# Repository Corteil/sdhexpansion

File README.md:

# SD Hexpansion

A Hexpansion for the [EMFCamp Tildagon badge](https://tildagon.badge.emfcamp.org/) which adds a MicroSD card socket in SPI mode.  The Hexpansion has an 8kB EEPROM and has a load switch for the SD card (there are a bunch of reasons SD cards can get "stuck" and are only recoverable by power cycling).  Details of the hardware design can be found in [the hardware docs](HARDWARE.md).

## Using your SD Hexpansion

To make use of the hexpansion right away without writing any of your own code, get an micro SD card
and plug it into a computer.  The card needs to be formatted as a FAT filesystem, that's what most
cards will be.

1. Make a folder on the SD card called `sdcard_apps`
2. Inside this folder you can place standard [Tildagon apps](https://tildagon.badge.emfcamp.org/tildagon-apps/)
3. Safely remove the SD card from your computer
4. Plug it into your hexpansion
5. Power up the badge
6. The hexpansion app for your SD card reader should pop up with three menu items "Mount", "Remove" and "Format".  Select the "Mount" option then exit the app (button F on the badge front-panel).
7. Now look at the bottom of the list of apps on the launcher, the apps on your SD card should be there and ready to go!

### Why "sdcard_apps"?
There's a [bug in micropython](https://github.com/emfcamp/badge-2024-software/issues/334) which means that `import` doesn't work properly if it includes the mount point of a FAT filesystem.  To work around this the driver EEPROM adds the mount-point (`sdcard` which is the name of the folder on the badge where all the files on your card will appear) to the system path.  That means that when `import` is run it searches in the SD card for micropython code.  If the folder where all the apps were installed on the SD card was just called `apps` it would have the same name as the default location on the badge itself and the software wouldn't know which of the two `apps` folders to look in.  The paths discussed here aren't magic, they are all defined in the EEPROM app which is run when the hexpansion is plugged in.

## Driver EEPROM

### Driver Hacking

If you want to modify the code that is in the driver app, you will need to follow the steps
here to get the modified code onto the hexpansion.

To squeeze the most out of the 8kB EEPROM on the hexpansion I've been compiling to
a `*.mpy` file, I've done this already but if you want to modify it you'll need to
do this step.  You need the [mpy-cross](https://pypi.org/project/mpy-cross/) tool
then you can simply run

    mpy-cross app.py

To setup a blank SD Hexpansion you need to plug it in to your badge and connect to the badge using [mpremote](https://docs.micropython.org/en/latest/reference/mpremote.html).

On the host change into the `app` directory of a checkout of this repository and run:

    mpremote mount .

This will connect to the running micropython system on your badge, hit `Ctrl-C` to
interrupt the normal OS and get a Python prompt.  Make sure the SDHexpansion is in port 2 (the right hand side) and short out the write-protect pins to allow the EEPROM to be overwritten (I normally use a pair of tweezers, but a jumper wire or even a bent paperclip will probably do).  Then on the mpremote terminal type:

    import prepare_eeprom

And that's it, the code runs on import and should have set up the EEPROM and copied the app.  Reboop the badge and you should get a new app offering to let you "Mount", "Remove" or "Format" the SD card.

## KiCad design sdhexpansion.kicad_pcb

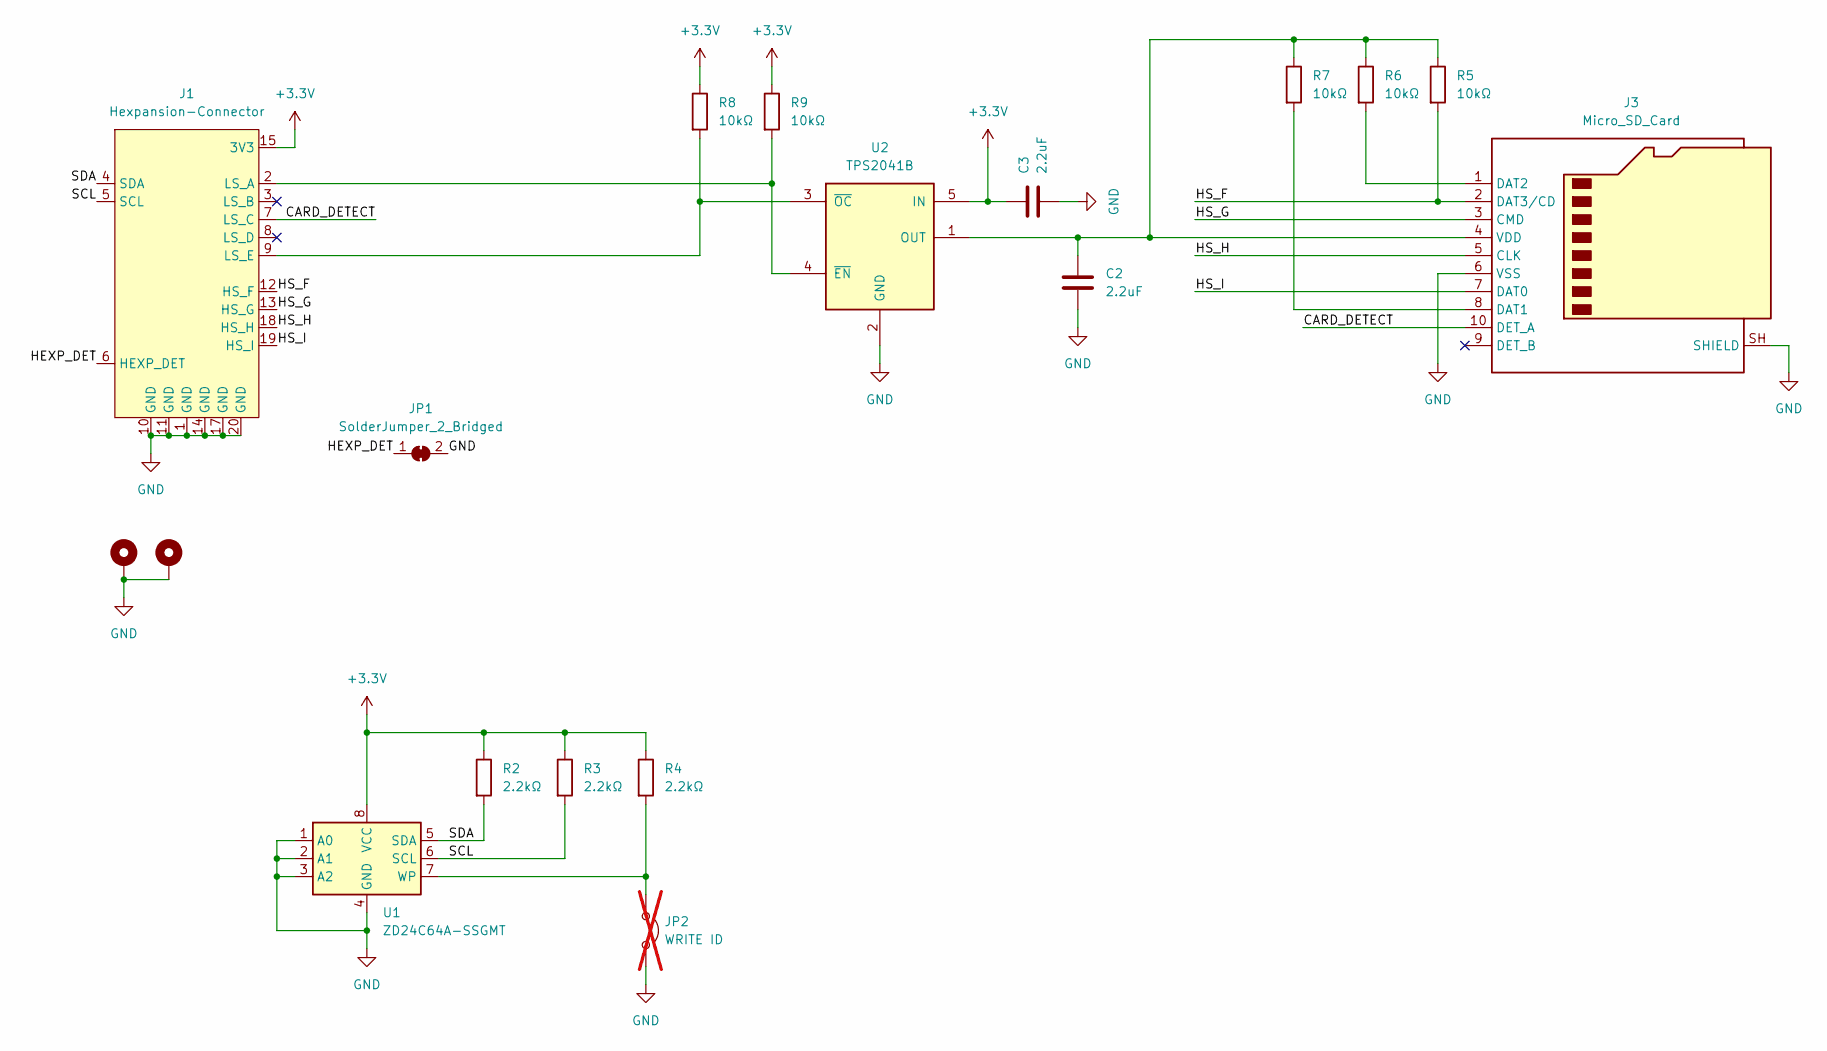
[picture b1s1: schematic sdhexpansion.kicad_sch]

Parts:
C2, C3: 2.2uF; C_0603_1608Metric; LCSC C23630
H1, H2: MountingHole_Pad; MountingHole_2.2mm_M2_Pad_Via
J1: Hexpansion-Connector; hexpansion-edge-connector
J3: Micro_SD_Card; MICRO-SD_XKTF-001C; LCSC C1121870
JP1: SolderJumper_2_Bridged; SolderJumper-2_P1.3mm_Bridged_RoundedPad1.0x1.5mm
JP2: WRITE ID; PinHeader_1x02_P2.54mm_Vertical; not fitted
R2, R3, R4: 2.2kΩ; R_0603_1608Metric; LCSC C4190
R5, R6, R7, R8, R9: 10kΩ; R_0603_1608Metric; LCSC C25804
U1: ZD24C64A-SSGMT; SOIC-8_3.9x4.9mm_P1.27mm; LCSC C2896793
U2: TPS2041B; SOT-23-5; LCSC C24593

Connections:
+3.3V: C3.2, J1.15 (3V3), J1.16 (3V3), R2.1, R3.1, R4.1, R8.1, R9.1, U1.8 (VCC), U2.5 (IN)
/CARD_DETECT: J1.7 (LS_C), J3.10 (DET_A)
/HEXP_DET: J1.6 (HEXP_DET), JP1.1 (A)
/HS_F: J1.12 (HS_F), J3.2 (DAT3/CD), R5.2
/HS_G: J1.13 (HS_G), J3.3 (CMD)
/HS_H: J1.18 (HS_H), J3.5 (CLK)
/HS_I: J1.19 (HS_I), J3.7 (DAT0)
/SCL: J1.5 (SCL), R3.2, U1.6 (SCL)
/SDA: J1.4 (SDA), R2.2, U1.5 (SDA)
GND: C2.1, C3.1, H1.1 (1_1), H2.1 (1_1), J1.1 (GND), J1.10 (GND), J1.11 (GND), J1.14 (GND), J1.17 (GND), J1.20 (GND), J3.6 (VSS), J3.SH (SHIELD), JP1.2 (B), JP2.2 (B), U1.1 (A0), U1.2 (A1), U1.3 (A2), U1.4 (GND), U2.2 (GND)
unnamed: J1.2 (LS_A), R9.2, U2.4 (~EN)
unnamed: J1.9 (LS_E), R8.2, U2.3 (~OC)
unnamed: J3.8 (DAT1), R7.2
unnamed: J3.1 (DAT2), R6.2
unnamed: C2.2, J3.4 (VDD), R5.1, R6.1, R7.1, U2.1 (OUT)
unnamed: JP2.1 (A), R4.2, U1.7 (WP)

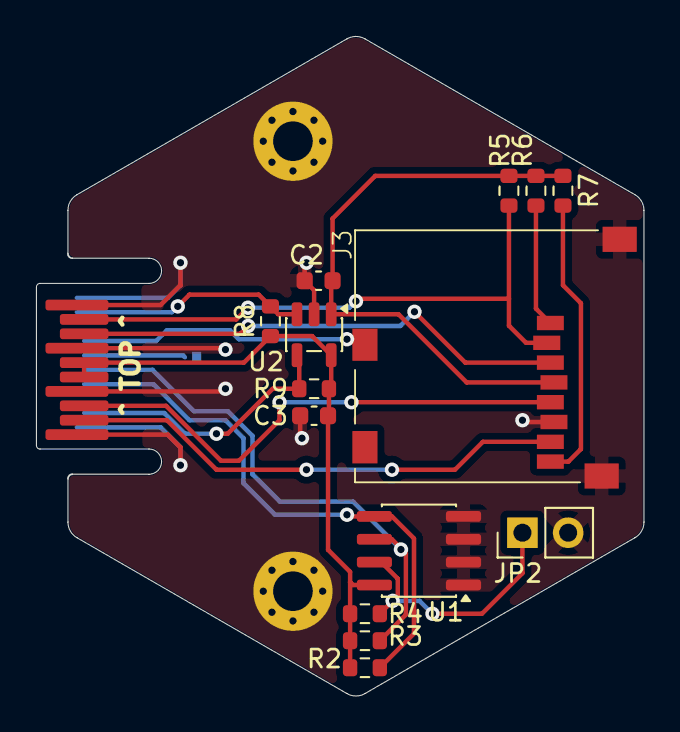
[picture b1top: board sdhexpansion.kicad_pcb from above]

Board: 2 copper layers, 33.7 x 36.6 mm, 18 parts (1 on the bottom side), 16 nets.

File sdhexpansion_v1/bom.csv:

Comment,Designator,Footprint,LCSC
2.2uF,"C2,C3",Capacitor_SMD:C_0603_1608Metric,C23630
2.2kΩ,"R2,R3,R4",Resistor_SMD:R_0603_1608Metric,C4190
Micro_SD_Card,J3,extras:MICRO-SD_XKTF-001C,C1121870
10kΩ,"R5,R6,R7,R8,R9",Resistor_SMD:R_0603_1608Metric,C25804
ZD24C64A-SSGMT,U1,Package_SO:SOIC-8_3.9x4.9mm_P1.27mm,C2896793
TPS2041B,U2,Package_TO_SOT_SMD:SOT-23-5,C24593

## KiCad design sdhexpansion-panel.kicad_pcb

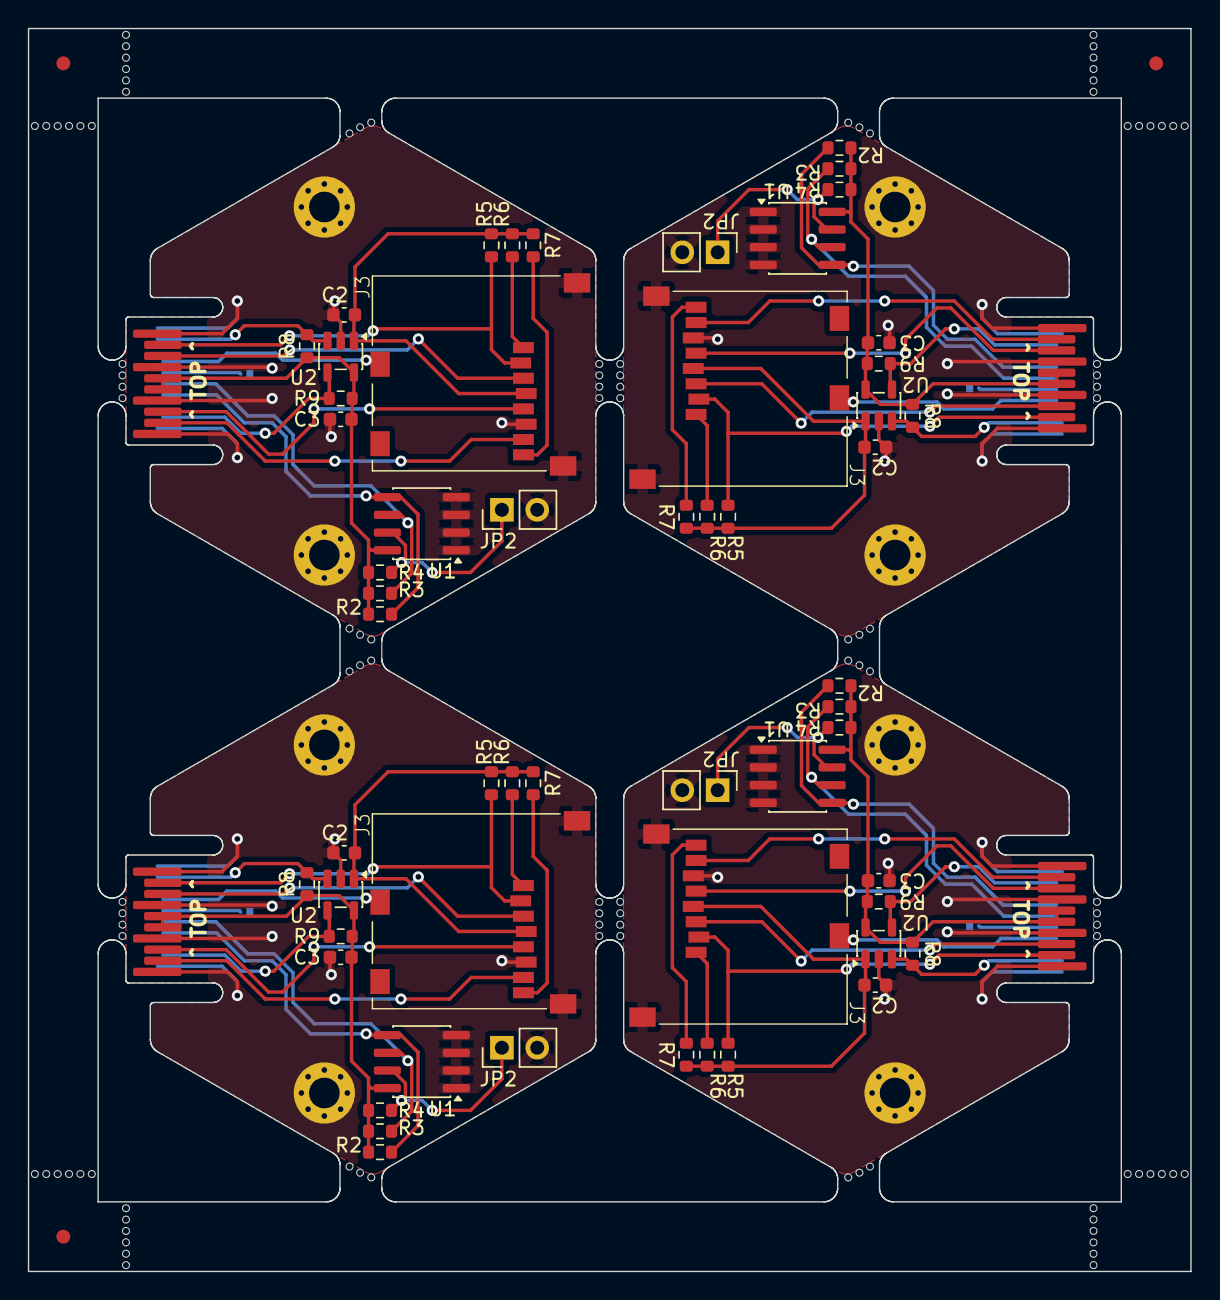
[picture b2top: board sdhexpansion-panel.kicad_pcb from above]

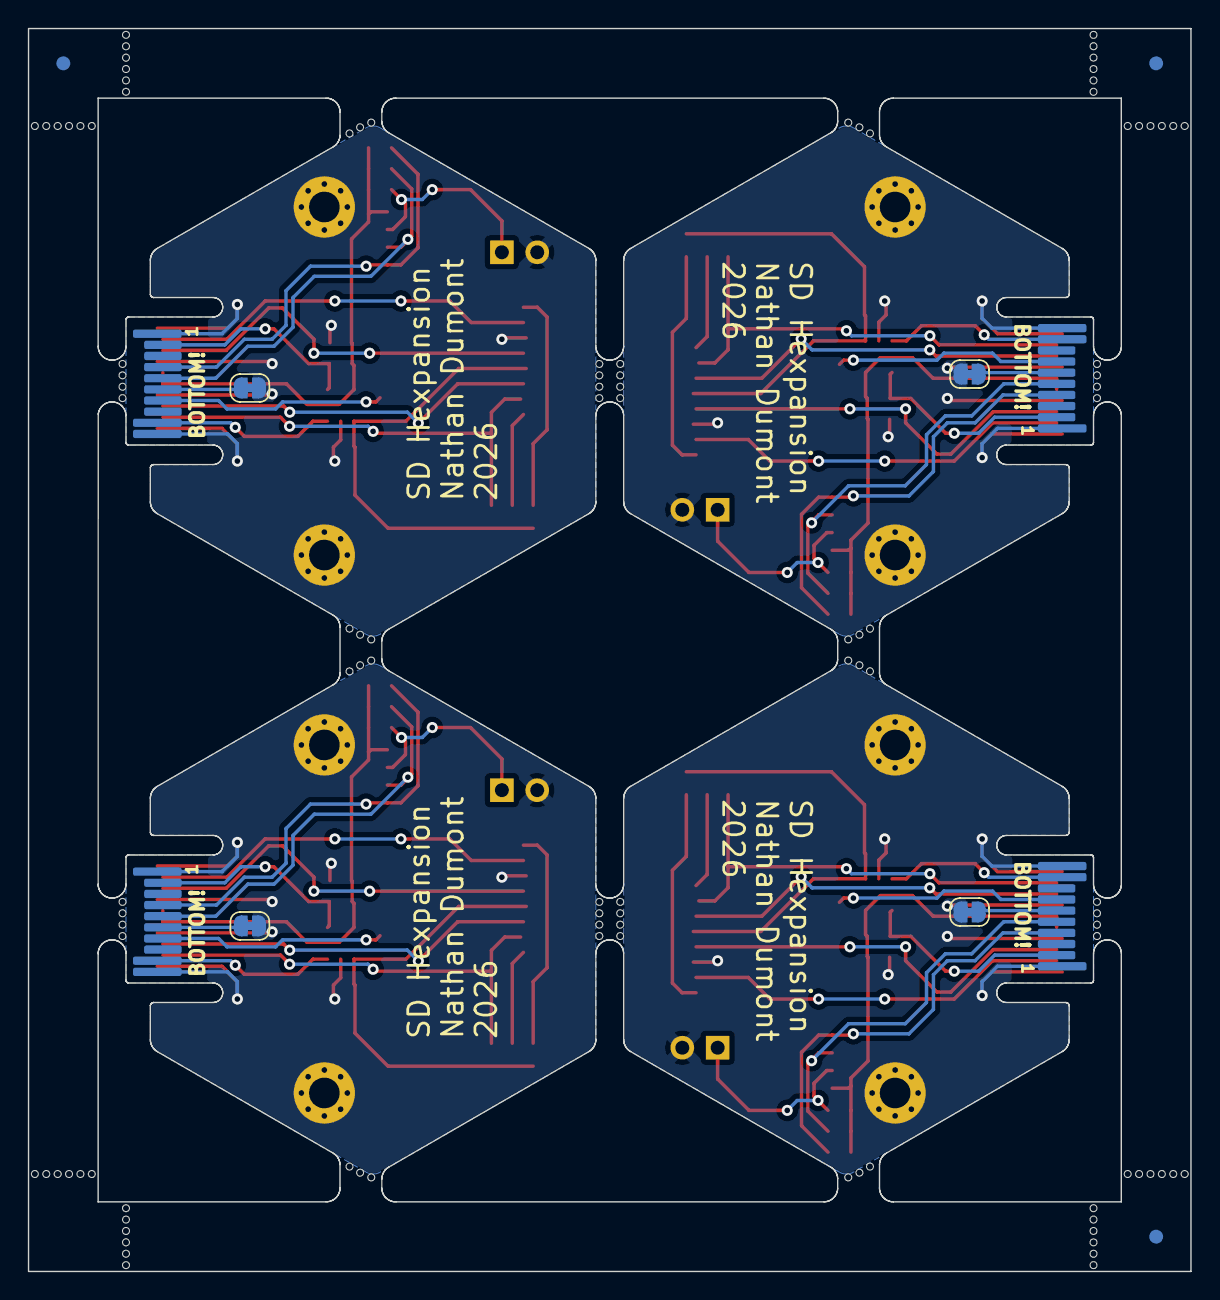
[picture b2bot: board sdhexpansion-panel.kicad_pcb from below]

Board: 2 copper layers, 83.5 x 89.3 mm, 182 parts (7 on the bottom side), 64 nets.

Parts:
C2, C2#2, C2#3, C2#4, C3, C3#2, C3#3, C3#4: 2.2uF; C_0603_1608Metric
H1, H1#2, H1#3, H1#4, H2, H2#2, H2#3, H2#4: MountingHole_Pad; MountingHole_2.2mm_M2_Pad_Via
J1, J1#2, J1#3, J1#4: Hexpansion-Connector; hexpansion-edge-connector
J3, J3#2, J3#3, J3#4: Micro_SD_Card; MICRO-SD_XKTF-001C
JP1, JP1#2, JP1#3, JP1#4: SolderJumper_2_Bridged; SolderJumper-2_P1.3mm_Bridged_RoundedPad1.0x1.5mm
JP2, JP2#2, JP2#3, JP2#4: WRITE ID; PinHeader_1x02_P2.54mm_Vertical
KiKit_FID_B_1, KiKit_FID_B_2, KiKit_FID_B_3: Fiducial
KiKit_FID_T_1, KiKit_FID_T_2, KiKit_FID_T_3: Fiducial
KiKit_MB_1_5, KiKit_MB_1_6, KiKit_MB_1_7, KiKit_MB_1_8, KiKit_MB_2_5, KiKit_MB_2_6, KiKit_MB_2_7, KiKit_MB_2_8, KiKit_MB_3_5, KiKit_MB_3_6, KiKit_MB_3_7, KiKit_MB_4_5, KiKit_MB_4_6, KiKit_MB_4_7, KiKit_MB_5_5, KiKit_MB_5_6, KiKit_MB_5_7, KiKit_MB_5_8, KiKit_MB_6_5, KiKit_MB_6_6, KiKit_MB_6_7, KiKit_MB_6_8, KiKit_MB_7_5, KiKit_MB_7_6, KiKit_MB_7_7, KiKit_MB_8_5, KiKit_MB_8_6, KiKit_MB_8_7, KiKit_MB_9_5, KiKit_MB_9_6, KiKit_MB_9_7, KiKit_MB_9_8, KiKit_MB_10_5, KiKit_MB_10_6, KiKit_MB_10_7, KiKit_MB_10_8, KiKit_MB_11_5, KiKit_MB_11_6, KiKit_MB_11_7, KiKit_MB_12_5, KiKit_MB_12_6, KiKit_MB_12_7, KiKit_MB_13_5, KiKit_MB_13_6, KiKit_MB_13_7, KiKit_MB_13_8, KiKit_MB_14_5, KiKit_MB_14_6, KiKit_MB_14_7, KiKit_MB_14_8, KiKit_MB_15_5, KiKit_MB_15_6, KiKit_MB_15_7, KiKit_MB_16_5, KiKit_MB_16_6, KiKit_MB_16_7, KiKit_MB_17_4, KiKit_MB_17_5, KiKit_MB_17_6, KiKit_MB_17_7, KiKit_MB_17_8, KiKit_MB_17_9, KiKit_MB_18_4, KiKit_MB_18_5, KiKit_MB_18_6, KiKit_MB_18_7, KiKit_MB_18_8, KiKit_MB_18_9, KiKit_MB_19_4, KiKit_MB_19_5, KiKit_MB_19_6, KiKit_MB_19_7, KiKit_MB_19_8, KiKit_MB_19_9, KiKit_MB_20_4, KiKit_MB_20_5, KiKit_MB_20_6, KiKit_MB_20_7, KiKit_MB_20_8, KiKit_MB_20_9, KiKit_MB_21_4, KiKit_MB_21_5, KiKit_MB_21_6, KiKit_MB_21_7, KiKit_MB_21_8, KiKit_MB_21_9, KiKit_MB_22_4, KiKit_MB_22_5, KiKit_MB_22_6, KiKit_MB_22_7, KiKit_MB_22_8, KiKit_MB_22_9, KiKit_MB_23_4, KiKit_MB_23_5, KiKit_MB_23_6, KiKit_MB_23_7, KiKit_MB_23_8, KiKit_MB_23_9, KiKit_MB_24_4, KiKit_MB_24_5, KiKit_MB_24_6, KiKit_MB_24_7, KiKit_MB_24_8, KiKit_MB_24_9: NPTH
R2, R2#2, R2#3, R2#4, R3, R3#2, R3#3, R3#4, R4, R4#2, R4#3, R4#4: 2.2kΩ; R_0603_1608Metric
R5, R5#2, R5#3, R5#4, R6, R6#2, R6#3, R6#4, R7, R7#2, R7#3, R7#4, R8, R8#2, R8#3, R8#4, R9, R9#2, R9#3, R9#4: 10kΩ; R_0603_1608Metric
U1, U1#2, U1#3, U1#4: ZD24C64A-SSGMT; SOIC-8_3.9x4.9mm_P1.27mm
U2, U2#2, U2#3, U2#4: TPS2041B; SOT-23-5

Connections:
Board_0-+3.3V: C3.2, J1.15 (3V3), J1.16 (3V3), R2.1, R3#3.1, R4#2.1, R8#4.1, R9#3.1, U1#4.8 (VCC), U2#3.5 (IN)
Board_0-/CARD_DETECT: J1.7 (LS_C), J3#4.10 (DET_A)
Board_0-/HEXP_DET: J1.6 (HEXP_DET), JP1#4.1 (A)
Board_0-/HS_F: J1.12 (HS_F), J3#4.2 (DAT3/CD), R5.2
Board_0-/HS_G: J1.13 (HS_G), J3#4.3 (CMD)
Board_0-/HS_H: J1.18 (HS_H), J3#4.5 (CLK)
Board_0-/HS_I: J1.19 (HS_I), J3#4.7 (DAT0)
Board_0-/SCL: J1.5 (SCL), R3#3.2, U1#4.6 (SCL)
Board_0-/SDA: J1.4 (SDA), R2.2, U1#4.5 (SDA)
Board_0-GND: C2#2.1, C3.1, H1#2.1 (1_1), H2.1 (1_1), J1.1 (GND), J1.10 (GND), J1.11 (GND), J1.14 (GND), J1.17 (GND), J1.20 (GND), J3#4.6 (VSS), J3#4.SH (SHIELD), JP1#4.2 (B), JP2.2 (B), U1#4.1 (A0), U1#4.2 (A1), U1#4.3 (A2), U1#4.4 (GND), U2#3.2 (GND)
Board_0-Net-(J1-LS_A): J1.2 (LS_A), R9#3.2, U2#3.4 (~EN)
Board_0-Net-(J1-LS_E): J1.9 (LS_E), R8#4.2, U2#3.3 (~OC)
Board_0-Net-(J3-DAT1): J3#4.8 (DAT1), R7#4.2
Board_0-Net-(J3-DAT2): J3#4.1 (DAT2), R6.2
Board_0-Net-(J3-VDD): C2#2.2, J3#4.4 (VDD), R5.1, R6.1, R7#4.1, U2#3.1 (OUT)
Board_0-Net-(JP2-A): JP2.1 (A), R4#2.2, U1#4.7 (WP)
Board_1-+3.3V: C3#3.2, J1#2.15 (3V3), J1#2.16 (3V3), R2#4.1, R3.1, R4#3.1, R8#2.1, R9.1, U1.8 (VCC), U2#4.5 (IN)
Board_1-/CARD_DETECT: J1#2.7 (LS_C), J3#2.10 (DET_A)
Board_1-/HEXP_DET: J1#2.6 (HEXP_DET), JP1.1 (A)
Board_1-/HS_F: J1#2.12 (HS_F), J3#2.2 (DAT3/CD), R5#3.2
Board_1-/HS_G: J1#2.13 (HS_G), J3#2.3 (CMD)
Board_1-/HS_H: J1#2.18 (HS_H), J3#2.5 (CLK)
Board_1-/HS_I: J1#2.19 (HS_I), J3#2.7 (DAT0)
Board_1-/SCL: J1#2.5 (SCL), R3.2, U1.6 (SCL)
Board_1-/SDA: J1#2.4 (SDA), R2#4.2, U1.5 (SDA)
Board_1-GND: C2.1, C3#3.1, H1.1 (1_1), H2#2.1 (1_1), J1#2.1 (GND), J1#2.10 (GND), J1#2.11 (GND), J1#2.14 (GND), J1#2.17 (GND), J1#2.20 (GND), J3#2.6 (VSS), J3#2.SH (SHIELD), JP1.2 (B), JP2#2.2 (B), U1.1 (A0), U1.2 (A1), U1.3 (A2), U1.4 (GND), U2#4.2 (GND)
Board_1-Net-(J1-LS_A): J1#2.2 (LS_A), R9.2, U2#4.4 (~EN)
Board_1-Net-(J1-LS_E): J1#2.9 (LS_E), R8#2.2, U2#4.3 (~OC)
Board_1-Net-(J3-DAT1): J3#2.8 (DAT1), R7.2
Board_1-Net-(J3-DAT2): J3#2.1 (DAT2), R6#2.2
Board_1-Net-(J3-VDD): C2.2, J3#2.4 (VDD), R5#3.1, R6#2.1, R7.1, U2#4.1 (OUT)
Board_1-Net-(JP2-A): JP2#2.1 (A), R4#3.2, U1.7 (WP)
Board_2-+3.3V: C3#4.2, J1#4.15 (3V3), J1#4.16 (3V3), R2#3.1, R3#2.1, R4.1, R8.1, R9#2.1, U1#3.8 (VCC), U2.5 (IN)
Board_2-/CARD_DETECT: J1#4.7 (LS_C), J3#3.10 (DET_A)
Board_2-/HEXP_DET: J1#4.6 (HEXP_DET), JP1#3.1 (A)
Board_2-/HS_F: J1#4.12 (HS_F), J3#3.2 (DAT3/CD), R5#2.2
Board_2-/HS_G: J1#4.13 (HS_G), J3#3.3 (CMD)
Board_2-/HS_H: J1#4.18 (HS_H), J3#3.5 (CLK)
Board_2-/HS_I: J1#4.19 (HS_I), J3#3.7 (DAT0)
Board_2-/SCL: J1#4.5 (SCL), R3#2.2, U1#3.6 (SCL)
Board_2-/SDA: J1#4.4 (SDA), R2#3.2, U1#3.5 (SDA)
Board_2-GND: C2#4.1, C3#4.1, H1#3.1 (1_1), H2#3.1 (1_1), J1#4.1 (GND), J1#4.10 (GND), J1#4.11 (GND), J1#4.14 (GND), J1#4.17 (GND), J1#4.20 (GND), J3#3.6 (VSS), J3#3.SH (SHIELD), JP1#3.2 (B), JP2#4.2 (B), U1#3.1 (A0), U1#3.2 (A1), U1#3.3 (A2), U1#3.4 (GND), U2.2 (GND)
Board_2-Net-(J1-LS_A): J1#4.2 (LS_A), R9#2.2, U2.4 (~EN)
Board_2-Net-(J1-LS_E): J1#4.9 (LS_E), R8.2, U2.3 (~OC)
Board_2-Net-(J3-DAT1): J3#3.8 (DAT1), R7#2.2
Board_2-Net-(J3-DAT2): J3#3.1 (DAT2), R6#4.2
Board_2-Net-(J3-VDD): C2#4.2, J3#3.4 (VDD), R5#2.1, R6#4.1, R7#2.1, U2.1 (OUT)
Board_2-Net-(JP2-A): JP2#4.1 (A), R4.2, U1#3.7 (WP)
Board_3-+3.3V: C3#2.2, J1#3.15 (3V3), J1#3.16 (3V3), R2#2.1, R3#4.1, R4#4.1, R8#3.1, R9#4.1, U1#2.8 (VCC), U2#2.5 (IN)
Board_3-/CARD_DETECT: J1#3.7 (LS_C), J3.10 (DET_A)
Board_3-/HEXP_DET: J1#3.6 (HEXP_DET), JP1#2.1 (A)
Board_3-/HS_F: J1#3.12 (HS_F), J3.2 (DAT3/CD), R5#4.2
Board_3-/HS_G: J1#3.13 (HS_G), J3.3 (CMD)
Board_3-/HS_H: J1#3.18 (HS_H), J3.5 (CLK)
Board_3-/HS_I: J1#3.19 (HS_I), J3.7 (DAT0)
Board_3-/SCL: J1#3.5 (SCL), R3#4.2, U1#2.6 (SCL)
Board_3-/SDA: J1#3.4 (SDA), R2#2.2, U1#2.5 (SDA)
Board_3-GND: C2#3.1, C3#2.1, H1#4.1 (1_1), H2#4.1 (1_1), J1#3.1 (GND), J1#3.10 (GND), J1#3.11 (GND), J1#3.14 (GND), J1#3.17 (GND), J1#3.20 (GND), J3.6 (VSS), J3.SH (SHIELD), JP1#2.2 (B), JP2#3.2 (B), U1#2.1 (A0), U1#2.2 (A1), U1#2.3 (A2), U1#2.4 (GND), U2#2.2 (GND)
Board_3-Net-(J1-LS_A): J1#3.2 (LS_A), R9#4.2, U2#2.4 (~EN)
Board_3-Net-(J1-LS_E): J1#3.9 (LS_E), R8#3.2, U2#2.3 (~OC)
Board_3-Net-(J3-DAT1): J3.8 (DAT1), R7#3.2
Board_3-Net-(J3-DAT2): J3.1 (DAT2), R6#3.2
Board_3-Net-(J3-VDD): C2#3.2, J3.4 (VDD), R5#4.1, R6#3.1, R7#3.1, U2#2.1 (OUT)
Board_3-Net-(JP2-A): JP2#3.1 (A), R4#4.2, U1#2.7 (WP)

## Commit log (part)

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2026-05-31 Initial commit, board files as ordered
2026-05-31 Added some documentation
2026-06-24 Basic bring-up code and some docs
    Waiting for some merges to allow hexpansion apps to be added to the
    launcher so you can safely remove the hexpansion.
